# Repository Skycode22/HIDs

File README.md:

# HIDs
## DISCLAIMER:
All projects not marked with "[FINAL]" are in a prototype stage, they may be in working order but require additional editing and fine-tuning.

HID (Human Interface Device) projects; Keyboards, trackballs, controllers of all sorts.

This repo is for the HID projects I have been working on and are making public for anyone to use, replicate, innovate, and otherwise utilize to their liking. If you make any new design changes/innovations, I would love to see them and potentially add them to the repository!

Feel free to message me with any questions or if you have any suggestions to make things better overall!

## Notable Projects Currently:

### Keyjoy
<table>
<tr>
<td>

</td>
<td>

</td>
</tr>
</table>

### MY75
<table>
<tr>
<td>

</td>
<td>

</td>
</tr>
</table>

### TrashTruck
<table>
<tr>
<td>

</td>
<td>

</td>
</tr>
</table>

### OpenOt
<table>
<tr>
<td>

</td>
<td>

</td>
</tr>
</table>

### Anguirus
<table>
<tr>
<td>

</td>
<td>

</td>
</tr>
</table>

### Gigan
<table>
<tr>
<td>

</td>
<td>

</td>
</tr>
</table>

### Mothra

### C64.pi

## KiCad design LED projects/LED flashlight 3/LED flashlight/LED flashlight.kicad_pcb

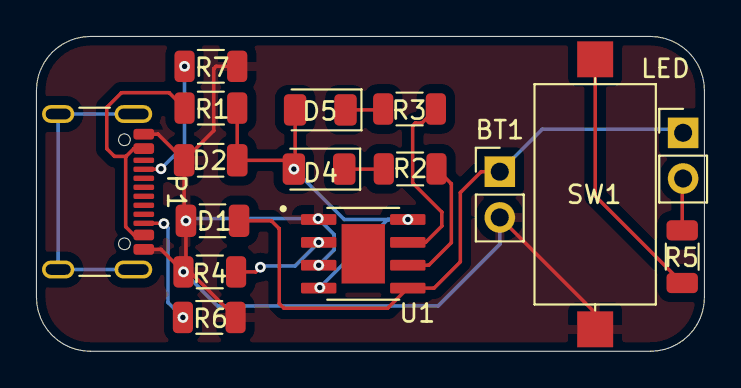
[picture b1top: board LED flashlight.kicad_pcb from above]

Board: 2 copper layers, 37.1 x 17.5 mm, 16 parts (0 on the bottom side), 11 nets.

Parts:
BT1: Battery; PinHeader_1x02_P2.54mm_Vertical
D1, D2: D_Capacitance; C_1206_3216Metric
D4, D5: LED; LED_1206_3216Metric
LED: Battery; PinHeader_1x02_P2.54mm_Vertical
P1: USB_C_Plug_USB2.0; USB_C_Receptacle_GCT_USB4105-xx-A_16P_TopMnt_Horizontal
R1, R2, R3, R4, R6, R7: R; R_1206_3216Metric
R5: R_US; R_1206_3216Metric
SW1: SW_Push; C_Axial_L12.0mm_D6.5mm_P15.00mm_Horizontal
U1: TP4056; SOP127P600X175-9N

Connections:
Earth: BT1.2 (-), D1.2 (A), D2.1 (K), P1.A1 (GND), P1.A12 (GND), P1.B1 (GND), P1.B12 (GND), R4.2, R6.2, R7.2, SW1.2, U1.1 (TEMP), U1.3 (GND)
unnamed: BT1.1 (+), D1.1 (K), LED.1 (+), U1.5 (BAT)
unnamed: D2.2 (A), D4.2 (A), D5.2 (A), R1.2, U1.4 (VCC), U1.8 (CE)
unnamed: LED.2 (-), R5.1
unnamed: D4.1 (K), R2.1
unnamed: D5.1 (K), R3.1
unnamed: P1.A4 (VBUS), P1.A9 (VBUS), P1.B4 (VBUS), P1.B9 (VBUS), R1.1
unnamed: R5.2, SW1.1
unnamed: R4.1, U1.2 (PROG)
unnamed: R3.2, U1.7 (~CHRG)
unnamed: R2.2, U1.6 (~STDBY)

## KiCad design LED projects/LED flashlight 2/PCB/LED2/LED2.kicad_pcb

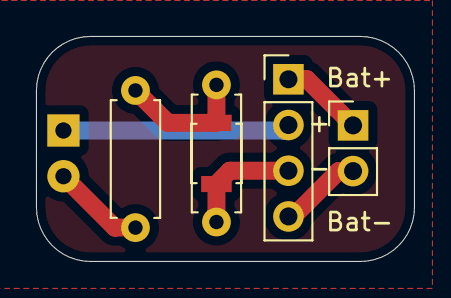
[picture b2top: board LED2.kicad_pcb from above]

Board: 2 copper layers, 21.0 x 12.5 mm, 6 parts (0 on the bottom side), 6 nets.

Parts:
BT1: Battery; PinHeader_1x02_P2.54mm_Vertical
BatteryChargeModule1: Battery Charge Module
D1: LED; LED_D5.0mm_Horizontal_O1.27mm_Z3.0mm
R1, R1#2: R_US; R_Axial_DIN0207_L6.3mm_D2.5mm_P7.62mm_Horizontal
SW1: SW_Push; SW_SPST_B3U-1000P

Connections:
unnamed: BT1.1 (+), BatteryChargeModule1.1 (Bat+)
unnamed: BT1.2 (-), BatteryChargeModule1.4 (-)
unnamed: BatteryChargeModule1.2 (Bat-), D1.1 (K)
unnamed: BatteryChargeModule1.3 (+), R1#2.1, SW1.2
unnamed: D1.2 (A), R1.1
unnamed: R1.2, R1#2.2, SW1.1

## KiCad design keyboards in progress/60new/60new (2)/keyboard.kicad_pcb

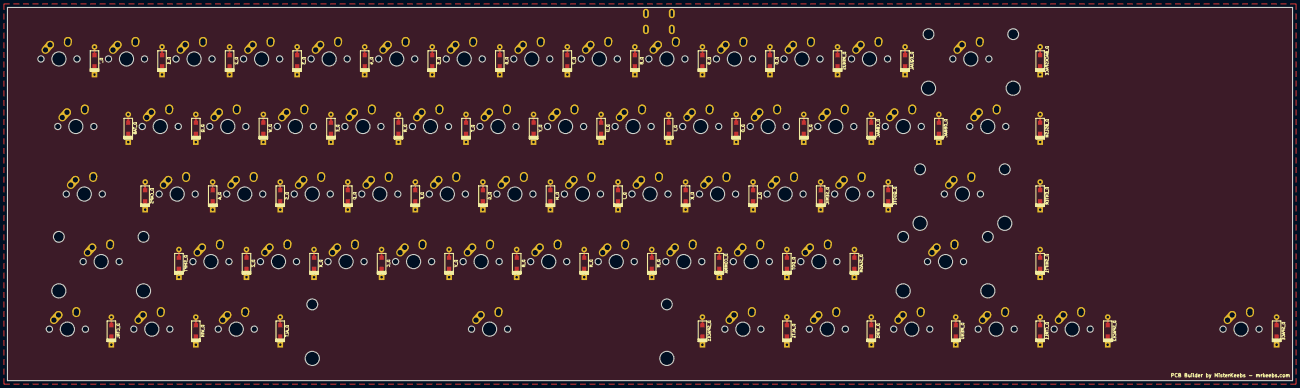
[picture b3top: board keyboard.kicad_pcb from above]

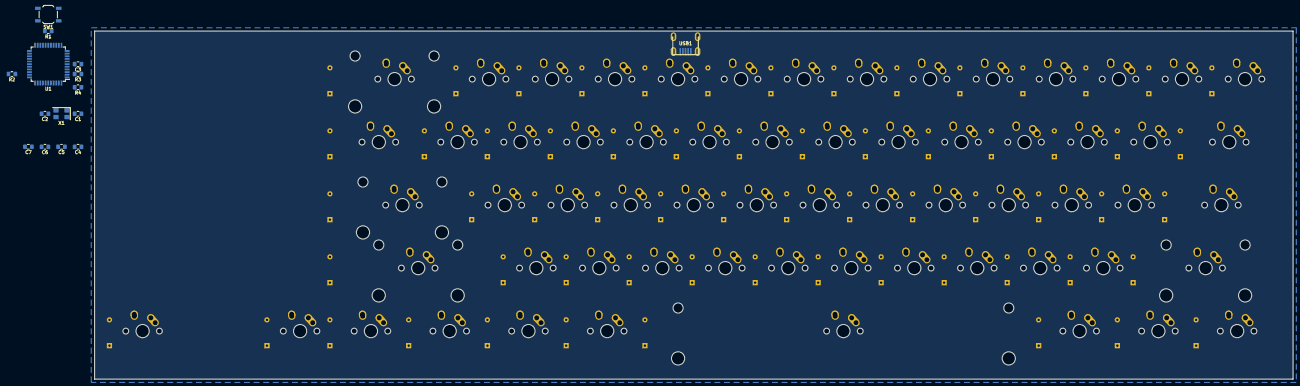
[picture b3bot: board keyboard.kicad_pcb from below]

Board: 2 copper layers, 362.4 x 105.2 mm, 141 parts (15 on the bottom side), 93 nets, no tracks yet.

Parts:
C1, C2, C3, C4, C5, C6, C7: 22pF; C_0805_2012Metric_Pad1.15x1.40mm_HandSolder
D_0, D_1, D_2, D_3, D_4, D_5, D_6, D_7, D_8, D_9: D; D_SOD123_axial
D_A: D; D_SOD123_axial
D_ALT, D_ALT1: D; D_SOD123_axial
D_B: D; D_SOD123_axial
D_BACKSPACE: D; D_SOD123_axial
D_BSLSH: D; D_SOD123_axial
D_C: D; D_SOD123_axial
D_CAPS: D; D_SOD123_axial
D_CBRAC: D; D_SOD123_axial
D_COMMA: D; D_SOD123_axial
D_CTRL, D_CTRL1: D; D_SOD123_axial
D_D: D; D_SOD123_axial
D_DOT: D; D_SOD123_axial
D_E: D; D_SOD123_axial
D_ENTER: D; D_SOD123_axial
D_EQUAL: D; D_SOD123_axial
D_F: D; D_SOD123_axial
D_G: D; D_SOD123_axial
D_H: D; D_SOD123_axial
D_I: D; D_SOD123_axial
D_J: D; D_SOD123_axial
D_K: D; D_SOD123_axial
D_L: D; D_SOD123_axial
D_M: D; D_SOD123_axial
D_MENU: D; D_SOD123_axial
D_MINUS: D; D_SOD123_axial
D_N: D; D_SOD123_axial
D_O: D; D_SOD123_axial
D_OBRAC: D; D_SOD123_axial
D_P: D; D_SOD123_axial
D_Q: D; D_SOD123_axial
D_QUOTE: D; D_SOD123_axial
D_R: D; D_SOD123_axial
D_S: D; D_SOD123_axial
D_SEMIC: D; D_SOD123_axial
D_SHIFT, D_SHIFT1: D; D_SOD123_axial
D_SLASH: D; D_SOD123_axial
D_SPACE, D_SPACE1, D_SPACE2: D; D_SOD123_axial
D_T: D; D_SOD123_axial
D_TAB: D; D_SOD123_axial
D_U: D; D_SOD123_axial
D_V: D; D_SOD123_axial
D_W: D; D_SOD123_axial
D_WIN, D_WIN1: D; D_SOD123_axial
D_X: D; D_SOD123_axial
D_Y: D; D_SOD123_axial
D_Z: D; D_SOD123_axial
D_`: D; D_SOD123_axial
K_0, K_1, K_2, K_3, K_4, K_5, K_6, K_7, K_8, K_9: KEYSW; MX-1U-NoLED
K_A: KEYSW; MX-1U-NoLED
K_ALT, K_ALT1: KEYSW; MX-1.25U-NoLED
K_B: KEYSW; MX-1U-NoLED
K_BACKSPACE: KEYSW; MX-2U-NoLED
K_BSLSH: KEYSW; MX-1.5U-NoLED
K_C: KEYSW; MX-1U-NoLED
K_CAPS: KEYSW; MX-1.75U-NoLED
K_CBRAC: KEYSW; MX-1U-NoLED
K_COMMA: KEYSW; MX-1U-NoLED
K_CTRL, K_CTRL1: KEYSW; MX-1.25U-NoLED
K_D: KEYSW; MX-1U-NoLED
K_DOT: KEYSW; MX-1U-NoLED
K_E: KEYSW; MX-1U-NoLED
K_ENTER: KEYSW; MX-2.25U-NoLED
K_EQUAL: KEYSW; MX-1U-NoLED
K_F: KEYSW; MX-1U-NoLED
K_G: KEYSW; MX-1U-NoLED
K_H: KEYSW; MX-1U-NoLED
K_I: KEYSW; MX-1U-NoLED
K_J: KEYSW; MX-1U-NoLED
K_K: KEYSW; MX-1U-NoLED
K_L: KEYSW; MX-1U-NoLED
K_M: KEYSW; MX-1U-NoLED
K_MENU: KEYSW; MX-1.25U-NoLED
K_MINUS: KEYSW; MX-1U-NoLED
K_N: KEYSW; MX-1U-NoLED
K_O: KEYSW; MX-1U-NoLED
K_OBRAC: KEYSW; MX-1U-NoLED
K_P: KEYSW; MX-1U-NoLED
K_Q: KEYSW; MX-1U-NoLED
K_QUOTE: KEYSW; MX-1U-NoLED
K_R: KEYSW; MX-1U-NoLED
K_S: KEYSW; MX-1U-NoLED
K_SEMIC: KEYSW; MX-1U-NoLED
K_SHIFT: KEYSW; MX-2.25U-NoLED
K_SHIFT1: KEYSW; MX-2.75U-NoLED
K_SLASH: KEYSW; MX-1U-NoLED
K_SPACE, K_SPACE2: KEYSW; MX-1U-NoLED
K_SPACE1: KEYSW; MX-6.25U-NoLED
K_T: KEYSW; MX-1U-NoLED
K_TAB: KEYSW; MX-1.5U-NoLED
K_U: KEYSW; MX-1U-NoLED
K_V: KEYSW; MX-1U-NoLED
K_W: KEYSW; MX-1U-NoLED
K_WIN, K_WIN1: KEYSW; MX-1.25U-NoLED
K_X: KEYSW; MX-1U-NoLED
K_Y: KEYSW; MX-1U-NoLED
K_Z: KEYSW; MX-1U-NoLED
K_`: KEYSW; MX-1U-NoLED
R1, R2: 10k; R_0805_2012Metric_Pad1.15x1.40mm_HandSolder
R3, R4: 22; R_0805_2012Metric_Pad1.15x1.40mm_HandSolder
SW1: SW_PUSH; SW_SPST_TL3342
U1: ATMEGA32U4; TQFP-44_10x10mm_P0.8mm
USB1: Molex-0548190589; Molex-0548190589-Assembly
X1: XTAL_GND; Crystal_SMD_5032-4Pin_5.0x3.2mm

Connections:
/col0: K_CAPS.1, K_CTRL.1, K_SHIFT.1, K_TAB.1, K_`.1, U1.31
/col1: K_1.1, K_A.1, K_Q.1, K_WIN.1, K_Z.1, U1.27
/col2: K_2.1, K_ALT.1, K_S.1, K_W.1, K_X.1, U1.8
/col3: K_3.1, K_C.1, K_D.1, K_E.1, U1.28
/col4: K_4.1, K_F.1, K_R.1, K_V.1, U1.29
/col5: K_5.1, K_B.1, K_G.1, K_T.1, U1.12
/col6: K_6.1, K_H.1, K_N.1, K_SPACE1.1, K_Y.1, U1.22
/col7: K_7.1, K_J.1, K_M.1, K_U.1, U1.32
/col8: K_8.1, K_COMMA.1, K_I.1, K_K.1, U1.40
/col9: K_9.1, K_ALT1.1, K_DOT.1, K_L.1, K_O.1, U1.41
/col10: K_0.1, K_P.1, K_SEMIC.1, K_SLASH.1, K_WIN1.1, U1.30
/col11: K_CBRAC.1, K_MENU.1, K_MINUS.1, K_QUOTE.1, K_SHIFT1.1, U1.37
/col12: K_CTRL1.1, K_ENTER.1, K_EQUAL.1, K_OBRAC.1, K_SPACE.1, U1.38
/col13: K_BACKSPACE.1, K_BSLSH.1, K_SPACE2.1, U1.39
/row0: D_0.1, D_1.1, D_2.1, D_3.1, D_4.1, D_5.1, D_6.1, D_7.1, D_8.1, D_9.1, D_BACKSPACE.1, D_EQUAL.1, D_MINUS.1, D_`.1, U1.21
/row1: D_BSLSH.1, D_CBRAC.1, D_E.1, D_I.1, D_O.1, D_OBRAC.1, D_P.1, D_Q.1, D_R.1, D_T.1, D_TAB.1, D_U.1, D_W.1, D_Y.1, U1.20
/row2: D_A.1, D_CAPS.1, D_D.1, D_ENTER.1, D_F.1, D_G.1, D_H.1, D_J.1, D_K.1, D_L.1, D_QUOTE.1, D_S.1, D_SEMIC.1, U1.19
/row3: D_B.1, D_C.1, D_COMMA.1, D_DOT.1, D_M.1, D_N.1, D_SHIFT.1, D_SHIFT1.1, D_SLASH.1, D_SPACE.1, D_V.1, D_X.1, D_Z.1, U1.18
/row4: D_ALT.1, D_ALT1.1, D_CTRL.1, D_CTRL1.1, D_MENU.1, D_SPACE1.1, D_SPACE2.1, D_WIN.1, D_WIN1.1, U1.25
GND: C1.2, C2.2, C3.2, C4.2, C5.2, C6.2, C7.2, R2.2, SW1.1, U1.5, U1.15, U1.23, USB1.1, X1.2, X1.4
unnamed: C1.1, U1.16, X1.1
unnamed: C2.1, U1.17, X1.3
unnamed: C3.1, U1.6
unnamed: D_0.2, K_0.2
unnamed: D_1.2, K_1.2
unnamed: D_2.2, K_2.2
unnamed: D_3.2, K_3.2
unnamed: D_4.2, K_4.2
unnamed: D_5.2, K_5.2
unnamed: D_6.2, K_6.2
unnamed: D_7.2, K_7.2
unnamed: D_8.2, K_8.2
unnamed: D_9.2, K_9.2
unnamed: D_A.2, K_A.2
unnamed: D_ALT1.2, K_ALT1.2
unnamed: D_ALT.2, K_ALT.2
unnamed: D_B.2, K_B.2
unnamed: D_BACKSPACE.2, K_BACKSPACE.2
unnamed: D_BSLSH.2, K_BSLSH.2
unnamed: D_C.2, K_C.2
unnamed: D_CAPS.2, K_CAPS.2
unnamed: D_CBRAC.2, K_CBRAC.2
unnamed: D_COMMA.2, K_COMMA.2
unnamed: D_CTRL1.2, K_CTRL1.2
unnamed: D_CTRL.2, K_CTRL.2
unnamed: D_D.2, K_D.2
unnamed: D_DOT.2, K_DOT.2
unnamed: D_E.2, K_E.2
unnamed: D_ENTER.2, K_ENTER.2
unnamed: D_EQUAL.2, K_EQUAL.2
unnamed: D_F.2, K_F.2
unnamed: D_G.2, K_G.2
unnamed: D_H.2, K_H.2
unnamed: D_I.2, K_I.2
unnamed: D_J.2, K_J.2
unnamed: D_K.2, K_K.2
unnamed: D_L.2, K_L.2
unnamed: D_M.2, K_M.2
unnamed: D_MENU.2, K_MENU.2
unnamed: D_MINUS.2, K_MINUS.2
unnamed: D_N.2, K_N.2
unnamed: D_O.2, K_O.2
unnamed: D_OBRAC.2, K_OBRAC.2
unnamed: D_P.2, K_P.2
unnamed: D_Q.2, K_Q.2
unnamed: D_QUOTE.2, K_QUOTE.2
unnamed: D_R.2, K_R.2
unnamed: D_S.2, K_S.2
unnamed: D_SEMIC.2, K_SEMIC.2
unnamed: D_SHIFT1.2, K_SHIFT1.2
unnamed: D_SHIFT.2, K_SHIFT.2
unnamed: D_SLASH.2, K_SLASH.2
unnamed: D_SPACE1.2, K_SPACE1.2
unnamed: D_SPACE2.2, K_SPACE2.2
unnamed: D_SPACE.2, K_SPACE.2
unnamed: D_T.2, K_T.2
unnamed: D_TAB.2, K_TAB.2
unnamed: D_U.2, K_U.2
unnamed: D_V.2, K_V.2
unnamed: D_W.2, K_W.2
unnamed: D_WIN1.2, K_WIN1.2
unnamed: D_WIN.2, K_WIN.2
unnamed: D_X.2, K_X.2
unnamed: D_Y.2, K_Y.2
unnamed: D_Z.2, K_Z.2
unnamed: D_`.2, K_`.2
unnamed: R1.1, SW1.2, U1.13
unnamed: R2.1, U1.33
unnamed: R3.1, U1.3
unnamed: R4.1, U1.4
unnamed: R3.2, USB1.2
unnamed: R4.2, USB1.3
VCC: C4.1, C5.1, C6.1, C7.1, R1.2, U1.2, U1.14, U1.24, USB1.5

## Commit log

2022-05-07 Create CAD mouse
2022-07-15 OpenEx Rev1
2022-07-15 OpenOrtho
2022-07-31 Rev2 OpenEx
2022-08-01 youtube
2022-08-10 file consolidation
2022-09-15 fixed ground zone issue in original
2022-09-15 unzipped pics
2022-09-15 writeup and new project added
2022-09-16 mothra added
2022-09-17 3d files
2022-09-18 new project
2022-09-19 ang upd
2022-09-21 file update
2022-09-21 remove obsolete design
2022-10-01 updates made qmk added
2022-10-05 3d update
2022-10-08 resin 3d added
2022-10-09 case update
2022-10-23 lots o updates
2022-11-09 update for new kaiju
2022-11-13 some more boards
2022-12-02 openot update
2022-12-02 another openot update
2022-12-04 wiring fix
2022-12-11 qmk update
2022-12-12 major update new wiring to come
2022-12-12 libraries kicad
2022-12-19 wiring update
2022-12-19 openot pcb updates
2022-12-19 3d model updates
2022-12-20 keymap update
2022-12-20 model updates
2022-12-20 remove ref text kicad
2022-12-21 pictures added
2023-01-07 openot pcb update
2023-01-13 3d model update
2023-01-15 new keyboard
2023-01-16 new pr9oject
2023-01-17 pcb update
2023-01-17 pcb trace update
2023-01-18 new project update
2023-01-18 rpi pico update
2023-01-18 another ootstag update
2023-01-19 pcb update ootstag
2023-01-19 file organization
2023-01-20 updates to OOTstag v2
2023-01-20 updt
2023-01-22 organization update
2023-01-26 added encoder support
2023-01-27 diagram update
2023-02-01 3d file update
2023-02-06 naming update
2023-02-06 another naming update
2023-03-04 added personal 65% project
2023-03-05 model update
2023-03-05 microcontroller update
2023-03-05 keyboard microcontroller update
2023-03-05 wiring update, almost finished
2023-03-05 udapte
2023-03-05 wiring finalized
2023-03-05 pcb finished, added gerber files; 1st rev case finished
2023-03-05 screenshots
2023-03-06 qmk firmware
2023-03-06 space change
2023-03-06 hex file and via enable
2023-03-06 personal65
2023-03-06 some update
2023-03-06 some 3d update
2023-03-06 pic update
2023-03-09 another case revision
2023-03-11 firmware add
2023-03-14 more 3d file updates
2023-03-14 opened
2023-03-15 added project and pictures
2023-03-22 update project
2023-03-23 graphic added
2023-03-24 second copy made
2023-03-24 name change
2023-03-24 pcb file update
2023-03-31 macropad midi add
2023-03-31 moved midi macropad
2023-03-31 pcg leaf spring update
2023-04-03 files moved and rev 2 work
2023-04-13 trashtruck added
2023-04-13 trahtruck update
2023-04-14 lots o changes
2023-04-14 trash update
2023-04-16 app update
2023-04-16 pics added
2023-04-16 pcb update final
2023-04-16 step added
2023-04-17 some updates
2023-04-17 trashtruck V2 added and 3d files added
2023-04-17 3d files added
2023-04-17 render/animation update
2023-04-18 trash
2023-05-01 firmware update
2023-05-06 documentation
2023-05-07 pdf instructions
2023-05-08 Update fp-info-cache
2023-05-16 name update
2023-05-29 final
2023-05-29 front page
2023-06-05 fdgh
2023-08-08 addition
2023-08-14 dreamake
2023-08-14 asjkdh
2023-08-15 alicida keyboard
2023-08-15 dfgh
2023-08-21 progress rev1
2023-08-21 progress
2023-08-22 fghyuj
2023-08-24 alicida rev2
2023-08-25 alicida split progress
2023-08-28 revision update
2023-08-30 design update
2023-08-30 new project addition
2023-08-31 new keyboard project
2023-09-01 sefg
2023-09-01 fab update
2023-09-02 not final
2023-09-02 pics add
2023-09-02 handwired update
2023-09-02 store board update
2023-09-03 3d model update, final version for handwired
2023-09-04 not final yet
2023-09-10 pics
2023-09-11 3d case update
2023-09-18 convention update
2023-09-27 final keyjoy update for now
2023-10-18 kicad update
2024-04-29 led chip project start
2024-08-16 led project
2024-08-16 led2 update
2024-08-19 new led project
2024-08-26 stm new
